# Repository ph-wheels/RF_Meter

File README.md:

# Dual channel RF meter

A battery powered, two-channel RF millivolt / power meter built around an ESP32 and a 24-bit MAX11270 ADC. Measures from below −55 dBm up to +23 dBm (50 Ω), from below 10 MHz to beyond 1 GHz, with auto range, an A-B (difference) mode and correction tables kept in non-volatile memory.

How to use the display: [DISPLAY_HELP.md](DISPLAY_HELP.md).

## History

This project started, quite a few months ago, with a question about a replacement or source for suitable detector diodes for the Boonton RF millivolt meter. From that the idea was born to build a millivolt and/or power meter with one of the modern ADC chips available today. Since then a few test drawings and PCBs were made, up to the current V5 of the ADC board (now a 4-layer board).

The project is a combined effort with Jacques (VE2AZX, http://www.ve2azx.net), who had already developed a replacement board for the Boonton millivolt / power meter series that fixes the problem with the mechanical chopper. Without his valued contribution, experience, feedback and high-precision RF measurements this project would not exist.

## Hardware

The design is based on two main PCBs and a battery board, which also shields the ADC board when mounted on top of it.

**Control board.** Connection to the battery board, a flat cable to the ADC board and a TTL-level UART to an external USB serial interface, which is also used to flash the ESP32. The ESP32 drives the 3.5" 480×320 touch display, reads the rotary encoder, the touch screen and the on-board push buttons, and controls the ADC board. The meter is battery powered and should run for several hours from 2× 2000 mAh or larger cells. There is optional board space for a BMS unit. Charging is with a 2S 1A charger module or through a barrel jack, and an on-board regulator (3V3) supplies the MCU and display.

**ADC board.** Two SMA inputs and the flat cable to the control board; optionally a 2-pin Amphenol connector, like the Boonton instruments. It has three areas: the three input circuits, the multiplexer with the ADC chip, and the voltage and reference sources with control for the attenuator and optional panel LEDs.
- Channels A and B: 50 Ω termination, detector circuit and attenuator (this gives the +23 dBm range), into a differential low-noise ×1 amplifier.
- Channel C (components populated, but not used in the current firmware): only the differential 5M6 resistors, the attenuator and the differential amplifier, so it is not a 50 Ω input.

| Part | Notes |
|---|---|
| ESP32 | Arduino-ESP32, PlatformIO, FreeRTOS |
| ILI9488 480×320 SPI display (landscape) | via TFT_eSPI, 18-bit colour |
| XPT2046 touch | shares the SPI bus, CS and IRQ pins in `config.h` |
| MAX11270 24-bit ADC | shares the SPI bus (4 MHz, mode 0), RDYB on an interrupt pin, 3.3 V reference |
| Rotary encoder with push button | pins in `config.h` |
| ADC board | 4-layer (signal, ground, power, signal); gain and attenuator switched through the ADC's GPIO pins |

Pin assignments are listed at the top of `main.cpp` and defined in `config.h`; the TFT pins are in your TFT_eSPI `User_Setup.h`.

| Signal | GPIO |
|---|---|
| SPI bus (shared by TFT, touch and ADC) | SCK 18, MISO 19, MOSI 23 |
| Touch CS / IRQ | 16 / 32 |
| ADC CSB / RDYB | 5 / 4 |
| Encoder CLK / DT / SW | 34 / 33 / 35 (external pull-ups) |
| Battery voltage | 27 (through a divider) |
| Optional second UART | TX 22, RX 21 |

## Project status

The main development goals have been reached:

- a battery powered instrument with modern chips and a display large enough to be usable
- an input range from below −55 dBm up to +23 dBm
- a frequency range from below 10 MHz to beyond 1 GHz (flat within about ±0.13 dB from 10 to 100 MHz, corrected above)
- auto range over the entire input range
- correction tables loaded and kept in non-volatile memory

The **A-B mode** (difference between the channels) now works over all ranges: the meter switches between A and B by itself, auto ranges each channel separately and shows A, B and the difference in dB. The price is the update rate: every channel switch needs about 0.5 s to settle, so a full A/B update takes about 1.2 s. In a test with a splitter at 400 MHz the channels agreed within ±0.2 dB, and a 10 dB attenuator in one lead gave a 10 dB difference in both directions.

Future plans: none at the moment, other than an updated schematic based on a dual ADC chip, which would make the A-B mode 2× to 3× faster. That costs more to build because of the extra ADC and the SSR / mux chip.

Build instructions (how to build the ADC and control boards, and how to test and commission each board) will follow in the folder `Build`.

Paul (PE1FCB (ex))

## Features

- **Two channels (A, B)** with a measured spread of about 0.1 dB at 50 MHz. Channel C is in the software as a placeholder (its calibration is a copy of A); it is not a 50 Ω input.
- **Three ranges per channel** (gain ×1 with attenuator, ×4, ×16), manual or **auto range** with hysteresis.
- **Bipolar ADC mode**, so the offset of the front end can be negative and is not clipped. 125 samples per second.
- **Per-channel, per-range calibration** as a polynomial in log space, loaded as JSON over USB serial and kept in NVS.
- **Zero (floor) correction** per channel and range, set from the display or over serial.
- **A-B page:** automatically alternates between A and B, autoranges each separately and shows A, B and the difference in dB.
- **Frequency correction:** one dB table for 200 to 1200 MHz, selectable on the display.
- Battery indicator, noise bar, touch calibration, brightness control.

## Software layout

| File | Content |
|---|---|
| `main.cpp` | Tasks, UI pages, touch handling, ADC consumer, auto range, A-B scheduler, Zero |
| `config.h` | All settings: ADC mode, range mapping, auto-range thresholds, timing, pages, pins |
| `max11270.c/.h` | ADC driver (ISR, reader task, bipolar format, gain/attenuator/channel control) |
| `adc_dbm.cpp/.h` | Raw code → Vac and dBm, floor subtraction |
| `calib_json.cpp/.h` | JSON calibration over serial, NVS storage |
| `app_settings.cpp/.h` | Touch calibration storage |
| `board_corrections.h` | Reference voltage and detector correction factor |

### Tasks

| Task | Core / priority | Job |
|---|---|---|
| encoder | 1 / 6 | knob and push button |
| touch | 0 / 3 | touch buttons |
| ui | 0 / 4 | renders the page when the state changes (about 3 Hz on live pages) |
| adc consumer | 1 / 2 | settle hold, noise window, auto range, A-B, Zero data |
| MAX11270 reader | – / 3 | reads the ADC when RDYB falls |
| heartbeat, battery | 0 / 1 | LED and battery voltage |

### How a reading is made

1. The ADC converts at 125 SPS. The RDYB interrupt wakes the reader task, which reads the sample and queues it.
2. After any channel, range or attenuator change, samples are ignored for `SETTLE_HOLD_MS` (500 ms).
3. The mean of the last 10 settled samples is the reading; it also feeds auto range.
4. Net code = raw − Z (floor). `log10(Vac) = a0 + M + a1·x + a2·x² + a3·x³`, with `x = log10(net)`. Then `dBm = 10·log10(Vac² / (50 Ω · 1 mW))`. A code at or below the floor gives no reading (`---`).
5. The selected frequency adds its dB correction.

### Display and ADC share one SPI bus

A full screen push used to hold the bus about 110 ms and cost most of the ADC samples. The display is therefore sent in thin slices (`UI_PUSH_SLICE_ROWS`, `UI_PUSH_GAP_US`) and the driver skips stale ready tokens. Result: the full 125 samples per second arrive. With `ADC_RATE_DIAG 1` a `[RATE]` line on serial shows this every 2 s.

## Build

PlatformIO, Arduino-ESP32. Libraries: TFT_eSPI, XPT2046_Touchscreen, ArduinoJson 7. Set your TFT_eSPI `User_Setup.h` for the ILI9488 and the display pins. Serial monitor at 115200 baud.

Main switches in `config.h`:

| Setting | Meaning |
|---|---|
| `ADC_APPLY_CALIBRATION` | 1 = calibrated readings, 0 = RAW codes for measuring a new calibration (attenuator forced off) |
| `ADC_BIPOLAR` | 1 = bipolar mode (current), 0 = unipolar |
| `RANGEn_GAIN_STEP`, `RANGEn_ATTEN_ON` | gain and attenuator of each range |
| `AUTORANGE_*` | switch points (raw counts) and sample count for auto range |
| `SETTLE_HOLD_MS`, `NOISE_WINDOW_SAMPLES` | settle hold and averaging window |
| `ZERO_*` | Zero button interlocks and NVS saving |
| `ENABLE_PAGE_BARGRAPH` | brings the bargraph page back |
| `ADC_RATE_DIAG`, `SETTLE_TRACE` | diagnostic output on serial |

Auto-range thresholds are raw counts and only hold for the current gains, attenuator states and bipolar mode. Re-measure them after changing any of these.

## Calibration

1. Build with `ADC_APPLY_CALIBRATION 0` and take raw readings at a series of known levels per channel and range (50 MHz). In range 1 the attenuator must be on, so measure it in calibrated mode.
2. Fit a cubic polynomial per channel and range (log10 of the net code against log10 of the voltage). Quartic fits diverge outside the measured range.
3. Send the JSON over USB serial (see [DISPLAY_HELP.md](DISPLAY_HELP.md#loading-calibration-data-usb-serial-115200-baud)).
4. Terminate the inputs, warm up, and zero each range from the display.
5. Optional: measure the roll-off at 200 to 1200 MHz and load it as `F_COR`.

Current calibration: 50 MHz, bipolar, cubic fits, both channels flat to about ±0.13 dB from 10 to 100 MHz.

## Known limits

- The input has parasitic capacitance, a single-pole roll-off at roughly 820 MHz, which is independent of level. `F_COR` compensates it in software; above about 1 GHz the accuracy is limited by the front end, and the noise floor goes up by the correction.
- The floors drift by a few µV over hours (range 3 of B the most). Zero again after warm-up.
- Noise is front-end dominated, so a higher gain than ×16 does not help.
- Channel C is a placeholder (calibration copied from A) and has no measured calibration.
- Redrawing the display takes about 0.5 s per frame; it is throttled to keep the ADC supplied.

## Acknowledgements

A completely redesigned firmware is now available. Early tests look promising, showing:
Improved signal stability Cleaner code Solid task isolation between various hardware components and the menu system with parameter storage
This was made possible largely thanks to Espressif's ESP32 FreeRTOS implementation (with help of Claude) — a real game-changer for the codebase.

Have fun building!

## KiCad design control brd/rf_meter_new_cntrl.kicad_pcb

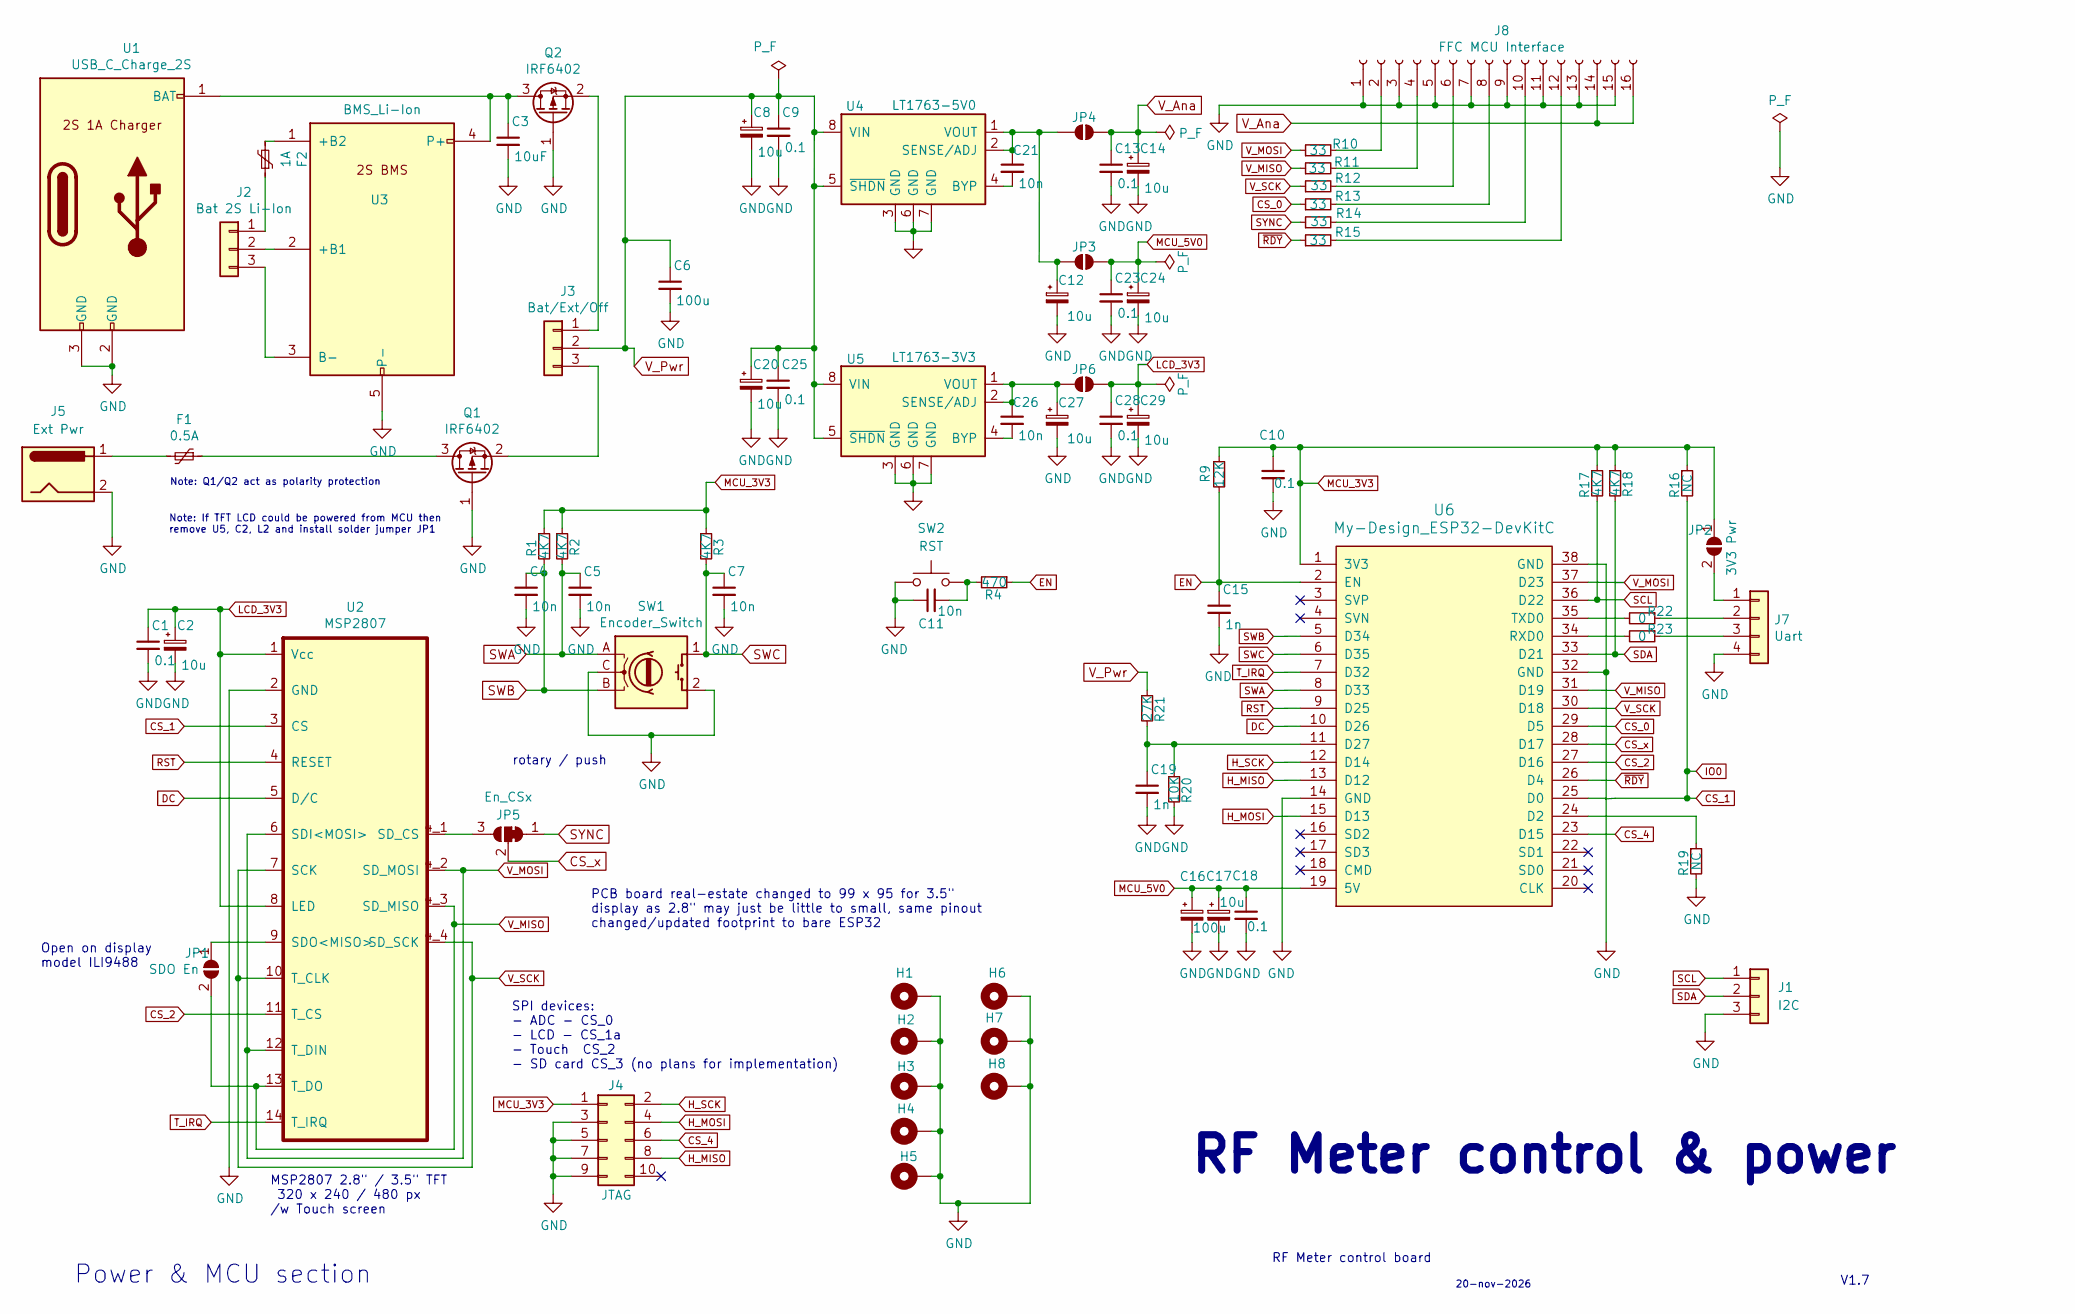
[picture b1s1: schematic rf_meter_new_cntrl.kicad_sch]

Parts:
C1, C9, C10, C13, C18, C23, C25, C28: 0.1; C_0805_2012Metric_Pad1.18x1.45mm_HandSolder
C2, C8, C12, C14, C17, C20, C24, C27, C29: 10u; C_0805_2012Metric_Pad1.18x1.45mm_HandSolder
C3: 10uF; C_0805_2012Metric_Pad1.18x1.45mm_HandSolder
C4, C5, C7, C11, C21, C26: 10n; C_0805_2012Metric_Pad1.18x1.45mm_HandSolder
C6, C16: 100u; CP_EIA-6032-20_AVX-F_HandSolder
C15, C19: 1n; C_0805_2012Metric_Pad1.18x1.45mm_HandSolder
F1: 0.5A; L_1206_3216Metric_Pad1.22x1.90mm_HandSolder
F2: 1A; L_1206_3216Metric_Pad1.22x1.90mm_HandSolder
H1, H2, H3, H4: MH; MountingHole_3.2mm_M3_Pad_Via
H5, H6, H7, H8: MH; MountingHole_3.2mm_M3_Pad
J1: I2C; PinHeader_1x03_P2.54mm_Vertical
J2: Bat 2S Li-Ion; PinHeader_1x3_P2.54_Drill1.1mm
J3: Bat/Ext/Off; PinHeader_1x3_P2.54_Drill1.1mm
J4: JTAG; Pin_Header_Straight_2x05_Pitch2.54mm
J5: Ext Pwr; BarrelJack_Horizontal
J7: Uart; Pin_Header_Straight_1x04_Pitch2.54mm
J8: FFC MCU Interface; TE_1-84952-6_1x16-1MP_P1.0mm_Horizontal
JP1: SDO En; SolderJumper-2_P1.3mm_Open_RoundedPad1.0x1.5mm
JP2: 3V3 Pwr; SolderJumper-2_P1.3mm_Open_RoundedPad1.0x1.5mm
JP3, JP4, JP6: SolderJumper-2_P1.3mm_Open_RoundedPad1.0x1.5mm
JP5: En_CSx; SolderJumper-3_P1.3mm_Bridged2Bar12_RoundedPad1.0x1.5mm
Q1, Q2: IRF6402; SOT-23-3
R1, R2, R3, R17, R18: 4K7; R_0805_2012Metric_Pad1.20x1.40mm_HandSolder
R4: 470; R_0805_2012Metric_Pad1.20x1.40mm_HandSolder
R9: 12K; R_0805_2012Metric_Pad1.20x1.40mm_HandSolder
R10, R11, R12, R13, R14, R15: 33; R_0805_2012Metric_Pad1.20x1.40mm_HandSolder
R16, R19: NC; R_0805_2012Metric_Pad1.20x1.40mm_HandSolder
R20: 10K; R_0805_2012Metric_Pad1.20x1.40mm_HandSolder
R21: 27K; R_0805_2012Metric_Pad1.20x1.40mm_HandSolder
R22, R23: 0; R_0805_2012Metric_Pad1.20x1.40mm_HandSolder
SW1: Encoder_Switch; Rotary_Encoder_Switched_PEC11R
SW2: RST; SW_Push_1P1T_NO_CK_KSC7xxJ
U1: USB_C_Charge_2S; USB-C_Charge_2S
U2: MSP2807; 3.5_TFT
U3: BMS_Li-Ion; HX-2S-A10
U4: LT1763-5V0; SOIC-8_5.3x6.2mm_P1.27mm
U5: LT1763-3V3; SOIC-8_5.3x6.2mm_P1.27mm
U6: My-Design_ESP32-DevKitC; ESP32_DevKitc_V4

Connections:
CS_0: R13.1, U6.29 (D5)
CS_1: R16.2, U2.3 (CS), U6.25 (D0)
CS_2: U2.11 (T_CS), U6.27 (D16)
CS_4: J4.6, U6.23 (D15)
CSx: JP5.2 (C), U6.28 (D17)
DC: U2.5 (D/C), U6.10 (D26)
EN: C15.1, R4.1, R9.2, U6.2 (EN)
GND: C1.2, C2.2, C3.2, C4.2, C5.2, C6.2, C7.2, C8.2, C9.2, C10.2, C11.1, C12.2, C13.2, C14.2, C15.2, C16.2, C17.2, C18.2, C19.2, C20.2, C23.2, C24.2, C25.2, C27.2, C28.2, C29.2, H1.1, H2.1, H3.1, H4.1, H5.1, H6.1, H7.1, H8.1, J1.3, J4.3, J4.5, J4.7, J4.9, J5.2, J5.3, J7.4, J8.1, J8.3, J8.5, J8.7, J8.9, J8.11, J8.13, J8.15, J8.MP, Q1.1 (G), Q2.1 (G), R19.2, R20.2, SW1.2, SW1.3, SW1.C, SW2.1, U1.2 (GND), U1.3 (GND), U2.2 (GND), U3.5 (P-), U4.3 (GND), U4.6 (GND), U4.7 (GND), U5.3 (GND), U5.6 (GND), U5.7 (GND), U6.14 (GND), U6.32 (GND), U6.38 (GND)
H_MISO: J4.8, U6.13 (D12)
H_MOSI: J4.4, U6.15 (D13)
H_SCK: J4.2, U6.12 (D14)
LCD_3V3: C1.1, C2.1, C28.1, C29.1, JP6.2 (B), U2.1 (Vcc), U2.8 (LED)
MCU_3V3: C10.1, J4.1, JP2.1 (A), R1.1, R2.1, R3.1, R9.1, R16.1, R17.1, R18.1, U6.1 (3V3)
MCU_5V0: C16.1, C17.1, C18.1, C23.1, C24.1, JP3.2 (B), U6.19 (5V)
unnamed: C11.2, R4.2, SW2.2
unnamed: F1.2, J5.1
unnamed: F2.1, J2.1
unnamed: J2.2, U3.2 (+B1)
unnamed: J2.3, U3.3 (B-)
unnamed: J3.1, Q2.2 (S)
unnamed: J3.3, Q1.2 (S)
unnamed: J7.1, JP2.2 (B)
unnamed: J7.2, R22.1
unnamed: J7.3, R23.1
unnamed: J8.2, R10.2
unnamed: J8.4, R11.2
unnamed: J8.6, R12.2
unnamed: J8.8, R13.2
unnamed: J8.10, R14.2
unnamed: J8.12, R15.2
unnamed: JP1.1 (A), U2.9 (SDO<MISO>)
unnamed: C12.1, C21.1, JP3.1 (A), JP4.1 (A), U4.1 (VOUT), U4.2 (SENSE/ADJ)
unnamed: JP5.3 (B), U2.4_1 (SD_CS)
unnamed: C26.1, C27.1, JP6.1 (A), U5.1 (VOUT), U5.2 (SENSE/ADJ)
unnamed: F1.1, Q1.3 (D)
unnamed: C3.1, Q2.3 (D), U1.1 (BAT), U3.4 (P+)
unnamed: F2.2, U3.1 (+B2)
unnamed: C21.2, U4.4 (BYP)
unnamed: C26.2, U5.4 (BYP)
unnamed: R19.1, U6.24 (D2)
unnamed: C19.1, R20.1, R21.2, U6.11 (D27)
unnamed: R23.2, U6.34 (RXD0)
unnamed: R22.2, U6.35 (TXD0)
RST: U2.4 (RESET), U6.9 (D25)
SCL: J1.1, R17.2, U6.36 (D22)
SDA: J1.2, R18.2, U6.33 (D21)
SWA: C5.1, R2.2, SW1.A, U6.8 (D33)
SWB: C4.1, R1.2, SW1.B, U6.5 (D34)
SWC: C7.1, R3.2, SW1.1, U6.6 (D35)
SYNC: JP5.1 (A), R14.1
T_IRQ: U2.14 (T_IRQ), U6.7 (D32)
V_Ana: C13.1, C14.1, J8.14, J8.16, JP4.2 (B)
V_MISO: JP1.2 (B), R11.1, U2.4_3 (SD_MISO), U2.13 (T_DO), U6.31 (D19)
V_MOSI: R10.1, U2.4_2 (SD_MOSI), U2.6 (SDI<MOSI>), U2.12 (T_DIN), U6.37 (D23)
V_Pwr: C6.1, C8.1, C9.1, C20.1, C25.1, J3.2, R21.1, U4.5 (~SHDN), U4.8 (VIN), U5.5 (~SHDN), U5.8 (VIN)
V_SCK: R12.1, U2.4_4 (SD_SCK), U2.7 (SCK), U2.10 (T_CLK), U6.30 (D18)
~RDY: R15.1, U6.26 (D4)

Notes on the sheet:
Open on display model ILI9488
Note: Q1/Q2 act as polarity protection
Power & MCU section
Note: If TFT LCD could be powered from MCU then remove U5, C2, L2 and install solder jumper JP1
V1.7
SPI devices: - ADC - CS_0 - LCD - CS_1a - Touch CS_2 - SD card CS_3 (no plans for implementation)
RF Meter control board
RF Meter control & power
PCB board real-estate changed to 99 x 95 for 3.5" display as 2.8" may just be little to small, same pinout changed/updated footprint to bare ESP32
MSP2807 2.8" / 3.5" TFT 320 x 240 / 480 px /w Touch screen
20-nov-2026
rotary / push

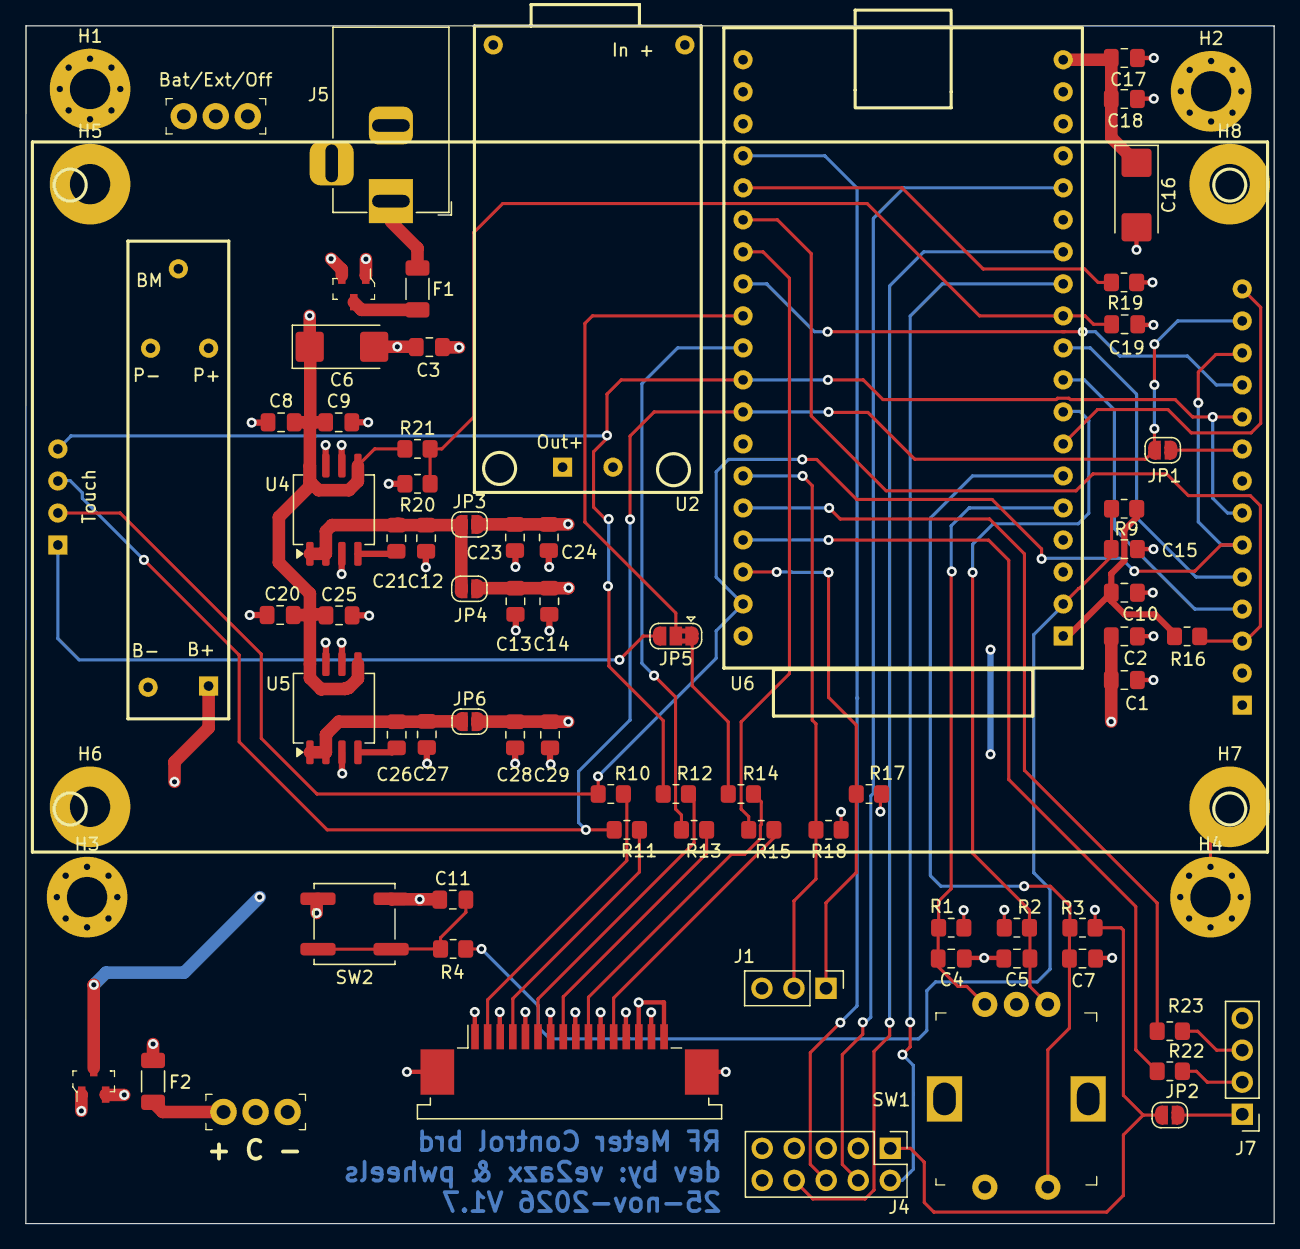
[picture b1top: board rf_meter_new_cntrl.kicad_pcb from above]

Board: 4 copper layers, 99.0 x 95.0 mm, 80 parts (0 on the bottom side), 57 nets.

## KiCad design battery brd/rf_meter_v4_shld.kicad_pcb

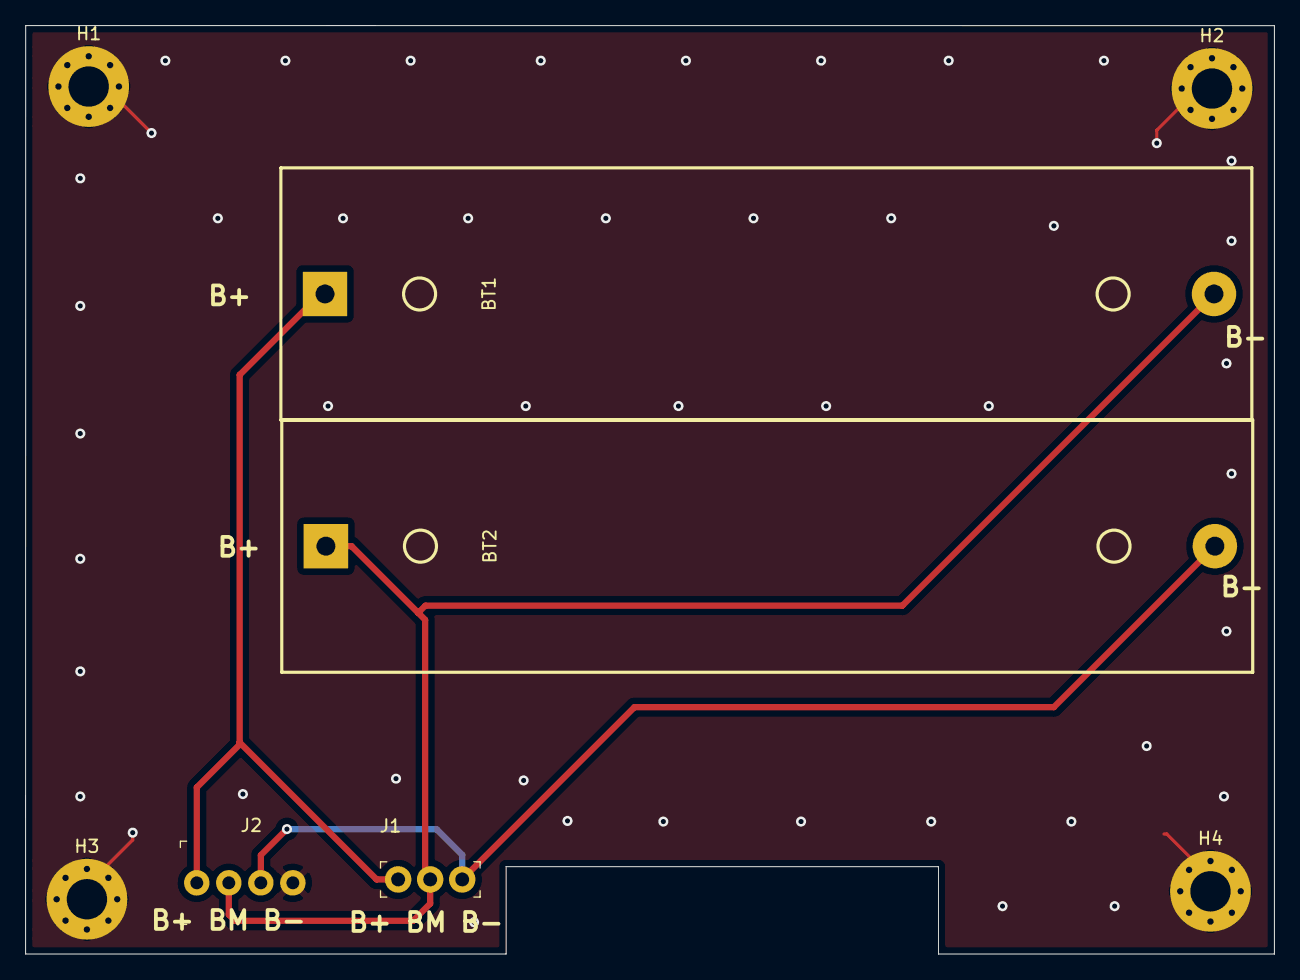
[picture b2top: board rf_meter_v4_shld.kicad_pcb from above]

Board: 2 copper layers, 99.0 x 73.6 mm, 8 parts (0 on the bottom side), 4 nets.

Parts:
BT1, BT2: Li-Ion 18650; Battery_Holder_2S
H1, H2, H3, H4: MountingHole; MountingHole_3.2mm_M3_Pad_Via
J1: Bat_Cntrl; PinHeader_1x3_P2.54_Drill1.1mm
J2: Bat_Test; PinHeader_1x4_P2.54mm_Drill1.02mm

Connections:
GND: H1.1, H2.1, H3.1, H4.1, J2.4
unnamed: BT1.1, J1.1, J2.1
unnamed: BT1.2, BT2.1, J1.2, J2.2
unnamed: BT2.2, J1.3, J2.3

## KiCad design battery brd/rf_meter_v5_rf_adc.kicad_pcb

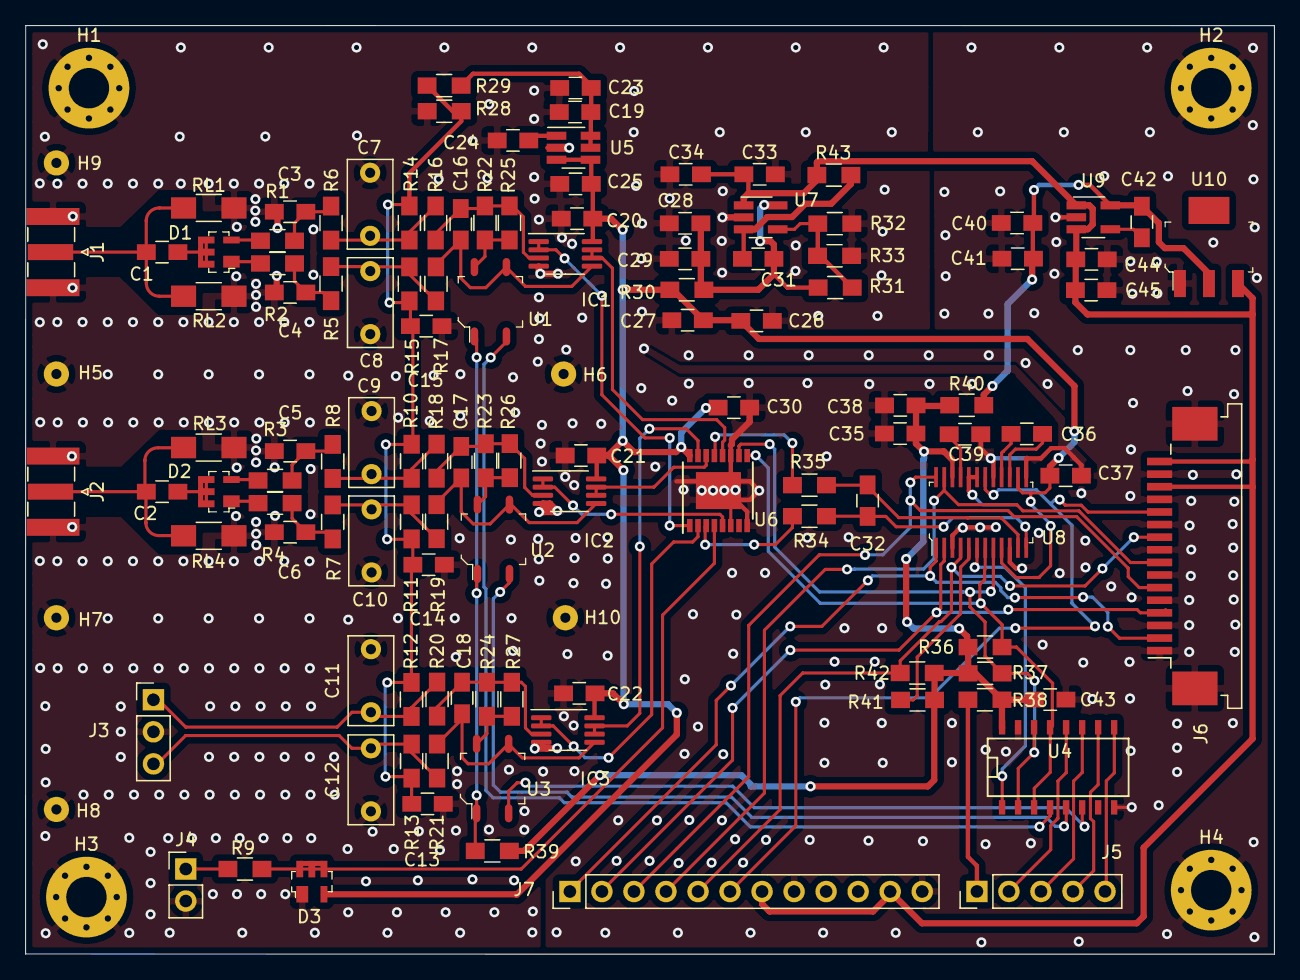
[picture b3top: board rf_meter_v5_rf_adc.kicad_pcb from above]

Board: 2 copper layers, 99.0 x 73.6 mm, 125 parts (0 on the bottom side), 73 nets.

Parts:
C1, C3, C4: 1n; C_0805_HandSoldering
C2, C5, C6: 1nF; C_0805_HandSoldering
C7, C8, C9, C10, C11, C12: 47n; C_Rect_L7.0mm_W3.5mm_P5.00mm
C13, C19, C20, C21, C22, C24, C25, C26, C28, C32, C33, C35, C36, C37, C40, C43, C44: 100n; C_0805_HandSoldering
C14, C15: 100nF; C_0805_HandSoldering
C16, C17, C18: 10n; C_0805_HandSoldering
C23, C27, C34, C38, C45: 10u; C_0805_HandSoldering
C29, C41: 4u7; C_0805_HandSoldering
C30: 0.1; C_0805_HandSoldering
C31, C42: 10nF; C_0805_HandSoldering
C39: 1u; C_0805_HandSoldering
D1, D2, D3: BAT62; SOT-143-4-SPC
H1, H2, H3, H4: MH; MountingHole_3.2mm_M3_Pad_Via
H5, H6, H7, H8, H9, H10: MH; SolderWirePad_single_0-8mmDrill
IC1, IC2, IC3: LTC2055; MSOP-8_3x3mm_P0.65mm
J1, J2: SMA; SMA_Samtec_SMA-J-P-X-ST-EM1_EdgeMount
J3: Amphenol 80-PC2F; Pin_Header_Straight_1x03_Pitch2.54mm
J4: Vtest; Pin_Header_Straight_1x02_Pitch2.54mm
J5: Panel Leds; Pin_Header_Straight_1x05_Pitch2.54mm
J6: FFC MCU Interface; TE_1-84952-6_1x16-1MP_P1.0mm_Horizontal
J7: MCU interface; Pin_Header_Straight_1x12_Pitch2.54mm
R1, R2, R3, R4: 110; R_0805_HandSoldering
R5, R6, R7, R8: 560; R_0805_HandSoldering
R9, R29, R34, R35: 1K; R_0805_HandSoldering
R10, R11, R12, R13, R14, R15: 5M6; R_0805_HandSoldering
R16, R17, R18, R19, R20, R21, R22, R23, R24, R25, R26, R27: 100K; R_0805_HandSoldering
R28: R_0805_HandSoldering
R30, R40, R43: 0; R_0805_HandSoldering
R31, R41, R42: 10K; R_0805_HandSoldering
R32: 20K; R_0805_HandSoldering
R33: 6K8; R_0805_HandSoldering
R36, R37: 4K7; R_0805_HandSoldering
R38, R39: 270; R_0805_HandSoldering
RL1, RL2: R_1206_HandSoldering
RL3, RL4: 100; R_1206_HandSoldering
U1, U2, U3: AQY212; SOP-4_W3.81mm
U4: 74LVC139; SO-16-N
U5: MAX6070 - 1V8; SOT-23-6_Handsoldering
U6: MAX4618; TSSOP-16-1EP_4.4x5mm_P0.65mm
U7: LT1761-BYP; SOT-23-5_HandSoldering
U8: MAX11270; TSSOP-24_W4.40mm
U9: LT1761-3.3; SOT-23-5_HandSoldering
U10: AMS1117-3.3; SOT-223-4

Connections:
AV3V6DD: C20.1, C21.1, C22.1, C25.1, C26.1, C27.1, C30.1, C37.1, D3.2, IC1.8, IC2.8, IC3.8, R30.1, U5.3, U5.4, U6.16, U8.9, U8.14
Att_A: U1.2, U4.4
Att_B: U2.2, U4.5
Att_C: U3.2, U4.6
Att_Ena: U4.1, U8.6
D3V3DD: C35.1, C38.1, C43.1, R36.1, R37.1, R38.1, R39.1, R40.1, R41.2, R42.2, U4.16, U8.22
D3V3LED: J5.1, R38.2
D3V3R: R39.2, U1.1, U2.1, U3.1
D7VDD: C33.1, C34.1, C44.1, C45.1, J6.14, J6.16, J7.7, J7.11, R43.2, U7.1, U9.1, U9.3, U10.3
GND: C3.2, C4.1, C5.2, C6.1, C7.2, C8.1, C9.2, C10.1, C11.2, C12.1, C13.2, C14.2, C15.2, C19.2, C20.2, C21.2, C22.2, C23.2, C24.2, C25.2, C26.2, C27.2, C28.2, C29.2, C30.2, C33.2, C34.2, C35.2, C37.2, C38.2, C39.2, C40.2, C41.2, C43.2, C44.2, C45.2, D3.1, H1.1, H2.1, H3.1, H4.1, H5.1, H6.1, H7.1, H8.1, H9.1, H10.1, IC1.4, IC2.4, IC3.4, J1.2, J2.2, J3.2, J4.2, J6.1, J6.3, J6.5, J6.7, J6.9, J6.11, J6.13, J6.15, J6.MP, J7.8, J7.12, R28.1, R32.1, R33.1, RL1.1, RL2.2, RL3.1, RL4.2, U4.8, U4.15, U5.2, U6.6, U6.8, U6.11, U6.17, U7.2, U8.3, U8.10, U8.13, U8.17, U8.19, U8.20, U9.2, U10.1
unnamed: C1.1, D1.3
unnamed: C1.2, J1.1, RL1.2, RL2.1
unnamed: C2.1, D2.3
unnamed: C2.2, J2.1, RL3.2, RL4.1
unnamed: C3.1, R1.2, R6.1
unnamed: C4.2, R2.2, R5.1
unnamed: C5.1, R3.2, R8.1
unnamed: C6.2, R4.2, R7.1
unnamed: C7.1, R6.2, R14.1, R16.1
unnamed: C8.2, R5.2, R15.2, R17.1
unnamed: C9.1, R8.2, R10.1, R18.1
unnamed: C10.2, R7.2, R11.2, R19.1
unnamed: C11.1, J3.1, R12.1, R20.1
unnamed: C12.2, J3.3, R13.2, R21.1
unnamed: C16.1, IC1.3, R16.2, R22.1, R25.1
unnamed: C16.2, IC1.5, R17.2, U1.3
unnamed: C17.1, IC2.3, R18.2, R23.1, R26.1
unnamed: C17.2, IC2.5, R19.2, U2.3
unnamed: C18.1, IC3.3, R20.2, R24.1, R27.1
unnamed: C18.2, IC3.5, R21.2, U3.3
unnamed: C19.1, C23.1, R29.1, U5.5, U5.6
unnamed: C24.1, U5.1
unnamed: C28.1, C29.1, C31.2, R30.2, R31.1, U7.5
unnamed: C31.1, R43.1, U7.3
unnamed: C32.1, R34.2, U8.12
unnamed: C32.2, R35.2, U8.11
unnamed: C36.1, U8.16
unnamed: C36.2, U8.15
unnamed: C39.1, U8.21
unnamed: C40.1, C41.1, C42.1, R40.2, U9.5, U10.2
unnamed: C42.2, U9.4
unnamed: D1.1, R2.1
unnamed: D1.2, R1.1
unnamed: D2.1, R4.1
unnamed: D2.2, R3.1
unnamed: D3.3, R9.2, U6.4
unnamed: IC1.1, IC1.2, U6.1
unnamed: IC1.6, IC1.7, U6.12
unnamed: IC2.1, IC2.2, U6.5
unnamed: IC2.6, IC2.7, U6.14
unnamed: IC3.1, IC3.2, U6.2
unnamed: IC3.6, IC3.7, U6.15
unnamed: J4.1, R9.1
unnamed: J5.2, U4.12
unnamed: J5.3, U4.11
unnamed: J5.4, U4.10
unnamed: J5.5, U4.9
unnamed: J6.2, J7.1, U8.1
unnamed: J6.4, J7.2, U8.2
unnamed: J6.6, J7.3, U8.24
unnamed: J6.8, J7.4, U8.23
unnamed: J6.10, J7.5, R42.1, U8.4
unnamed: J6.12, J7.6, U8.18
unnamed: R22.2, R25.2, U1.4
unnamed: R23.2, R26.2, U2.4
unnamed: R24.2, R27.2, U3.4
unnamed: R31.2, R32.2, R33.2, U7.4
unnamed: R34.1, U6.3
unnamed: R35.1, U6.13
unnamed: R36.2, U4.3, U4.13, U6.9, U8.7
unnamed: R37.2, U4.2, U4.14, U6.10, U8.8
unnamed: R41.1, U8.5
VPre: C13.1, C14.1, C15.1, R10.2, R11.1, R12.2, R13.1, R14.2, R15.1, R28.2, R29.2

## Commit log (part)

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2023-01-31 Create LICENSE
